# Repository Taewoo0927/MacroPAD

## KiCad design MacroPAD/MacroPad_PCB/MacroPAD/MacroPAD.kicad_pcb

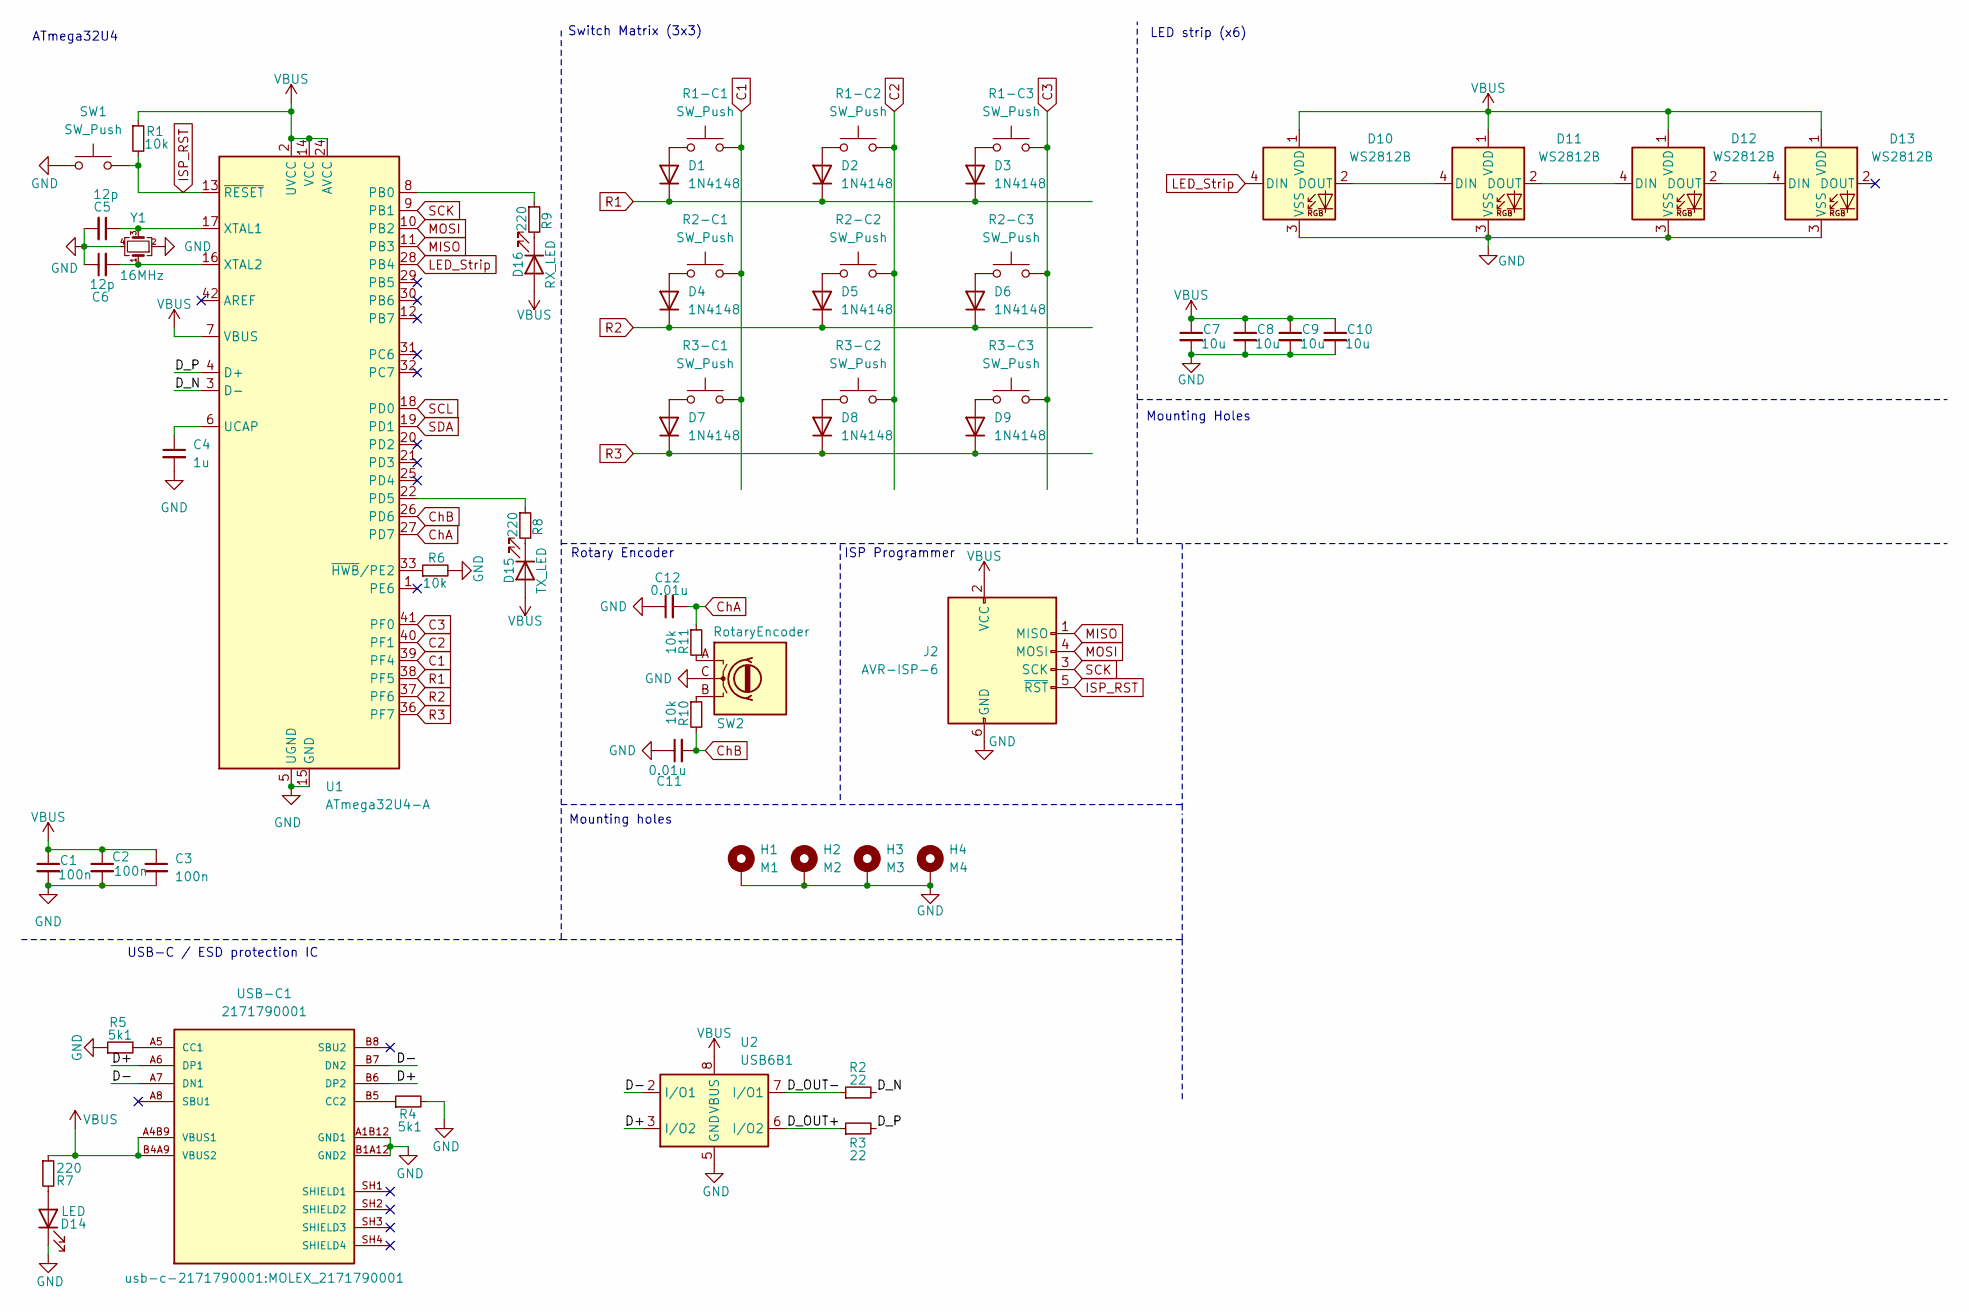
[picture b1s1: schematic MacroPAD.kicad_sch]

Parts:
C1, C2, C3: 100n; C_0603_1608Metric; MPN C0603C104K5RACTU
C4: 1u; C_0603_1608Metric; MPN CL10A105KB8NNNC
C5, C6: 12p; C_0603_1608Metric; MPN CL10C120JB8NNNC
C7, C8, C9, C10: 10u; C_0603_1608Metric; MPN C0603C106M8PACTU
C11, C12: 0.01u; C_0603_1608Metric; MPN C0603C103K5RACTU
D1, D2, D3, D4, D5, D6: 1N4148; D_SOD-123; MPN 1N4148W-13-F
D7, D8, D9: 1N4148; D_SOD-123
D10, D11, D12, D13: WS2812B; LED_WS2812B_PLCC4_5.0x5.0mm_P3.2mm; MPN COM-16347
D14: LED; LED_0805_2012Metric; MPN LG R971-KN-1-0-20-R18
D15: TX_LED; LED_1206_3216Metric; MPN LTST-C150YKT
D16: RX_LED; LED_1206_3216Metric; MPN LTST-C150KRKT
H1: M1; MountingHole_3.2mm_M3_Pad_Via
H2: M2; MountingHole_3.2mm_M3_Pad_Via
H3: M3; MountingHole_3.2mm_M3_Pad_Via
H4: M4; MountingHole_3.2mm_M3_Pad_Via
J2: AVR-ISP-6; IDC-Header_2x03_P2.54mm_Vertical; MPN 61200621621
R1: 10k; R_1206_3216Metric; MPN RC1206FR-0710KL
R1-C1, R1-C2, R1-C3, R2-C1, R2-C2, R2-C3, R3-C1, R3-C2, R3-C3: SW_Push; SW_Hotswap_Kailh_MX_1.00u; MPN PG151101S11
R2, R3: 22; R_0603_1608Metric; MPN RC0603FR-0722RL
R4, R5: 5k1; R_0603_1608Metric; MPN CR0603-FX-5101ELF
R6, R10, R11: 10k; R_0603_1608Metric; MPN RC0603FR-0710KL
R7: 220; R_0805_2012Metric; MPN CRGCQ0805F220R
R8, R9: 220; R_1206_3216Metric; MPN CRG1206F220R
SW1: SW_Push; SW_PUSH_6mm; MPN SKHHAKA010
SW2: RotaryEncoder; PEC12R-4XXXF-NXXXX_BRN; MPN PEC12R-4225F-N0024
U1: ATmega32U4-A; TQFP-44_10x10mm_P0.8mm; MPN ATmega32U4-A
U2: USB6B1; SOIC-8_3.9x4.9mm_P1.27mm; MPN USB6B1
USB-C1: 2171790001; MOLEX_2171790001; PARTREV A1
Y1: 16MHz; Crystal_SMD_0603-4Pin_6.0x3.5mm; MPN ECS-160-20-33-TR

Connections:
/D+: U2.3 (I/O2), USB-C1.A6 (DP1), USB-C1.B6 (DP2)
/D-: U2.2 (I/O1), USB-C1.A7 (DN1), USB-C1.B7 (DN2)
/D_N: R2.2, U1.3 (D-)
/D_OUT+: R3.1, U2.6 (I/O2)
/D_OUT-: R2.1, U2.7 (I/O1)
/D_P: R3.2, U1.4 (D+)
C1: R1-C1.2, R2-C1.2, R3-C1.2, U1.39 (PF4)
C2: R1-C2.2, R2-C2.2, R3-C2.2, U1.40 (PF1)
C3: R1-C3.2, R2-C3.2, R3-C3.2, U1.41 (PF0)
ChA: C12.2, R11.1, U1.27 (PD7)
ChB: C11.2, R10.2, U1.26 (PD6)
GND: C1.2, C2.2, C3.2, C4.2, C5.2, C6.1, C7.2, C8.2, C9.2, C10.2, C11.1, C12.1, D10.3 (VSS), D11.3 (VSS), D12.3 (VSS), D13.3 (VSS), D14.1 (K), H1.1, H2.1, H3.1, H4.1, J2.6 (GND), R4.2, R5.1, R6.2, SW1.1, SW2.C, U1.5 (UGND), U1.15 (GND), U1.23 (GND), U1.35 (GND), U1.43 (GND), U2.4 (GND), U2.5 (GND), USB-C1.A1B12 (GND1), USB-C1.B1A12 (GND2), Y1.2, Y1.4
ISP_RST: J2.5 (~RST), R1.2, SW1.2, U1.13 (~RESET)
LED_Strip: D10.4 (DIN), U1.28 (PB4)
MISO: J2.1 (MISO), U1.11 (PB3)
MOSI: J2.4 (MOSI), U1.10 (PB2)
unnamed: D1.2 (A), R1-C1.1
unnamed: D2.2 (A), R1-C2.1
unnamed: D3.2 (A), R1-C3.1
unnamed: D4.2 (A), R2-C1.1
unnamed: D5.2 (A), R2-C2.1
unnamed: D6.2 (A), R2-C3.1
unnamed: D7.2 (A), R3-C1.1
unnamed: D8.2 (A), R3-C2.1
unnamed: D9.2 (A), R3-C3.1
unnamed: D10.2 (DOUT), D11.4 (DIN)
unnamed: D11.2 (DOUT), D12.4 (DIN)
unnamed: D12.2 (DOUT), D13.4 (DIN)
unnamed: D14.2 (A), R7.2
unnamed: D15.1 (K), R8.2
unnamed: D16.1 (K), R9.2
unnamed: R10.1, SW2.B
unnamed: R11.2, SW2.A
unnamed: R9.1, U1.8 (PB0)
unnamed: R8.1, U1.22 (PD5)
unnamed: C4.1, U1.6 (UCAP)
unnamed: C5.1, U1.17 (XTAL1), Y1.3
unnamed: C6.2, U1.16 (XTAL2), Y1.1
unnamed: R6.1, U1.33 (~HWB/PE2)
unnamed: R5.2, USB-C1.A5 (CC1)
unnamed: R4.1, USB-C1.B5 (CC2)
R1: D1.1 (K), D2.1 (K), D3.1 (K), U1.38 (PF5)
R2: D4.1 (K), D5.1 (K), D6.1 (K), U1.37 (PF6)
R3: D7.1 (K), D8.1 (K), D9.1 (K), U1.36 (PF7)
SCK: J2.3 (SCK), U1.9 (PB1)
SCL: U1.18 (PD0)
SDA: U1.19 (PD1)
VBUS: C1.1, C2.1, C3.1, C7.1, C8.1, C9.1, C10.1, D10.1 (VDD), D11.1 (VDD), D12.1 (VDD), D13.1 (VDD), D15.2 (A), D16.2 (A), J2.2 (VCC), R1.1, R7.1, U1.2 (UVCC), U1.7 (VBUS), U1.14 (VCC), U1.24 (AVCC), U1.34 (VCC), U1.44 (AVCC), U2.1 (VBUS), U2.8 (VBUS), USB-C1.A4B9 (VBUS1), USB-C1.B4A9 (VBUS2)

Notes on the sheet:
ATmega32U4
USB-C / ESD protection IC
Mounting holes
LED strip (x6)
ISP Programmer
Rotary Encoder
Mounting Holes
Switch Matrix (3x3)

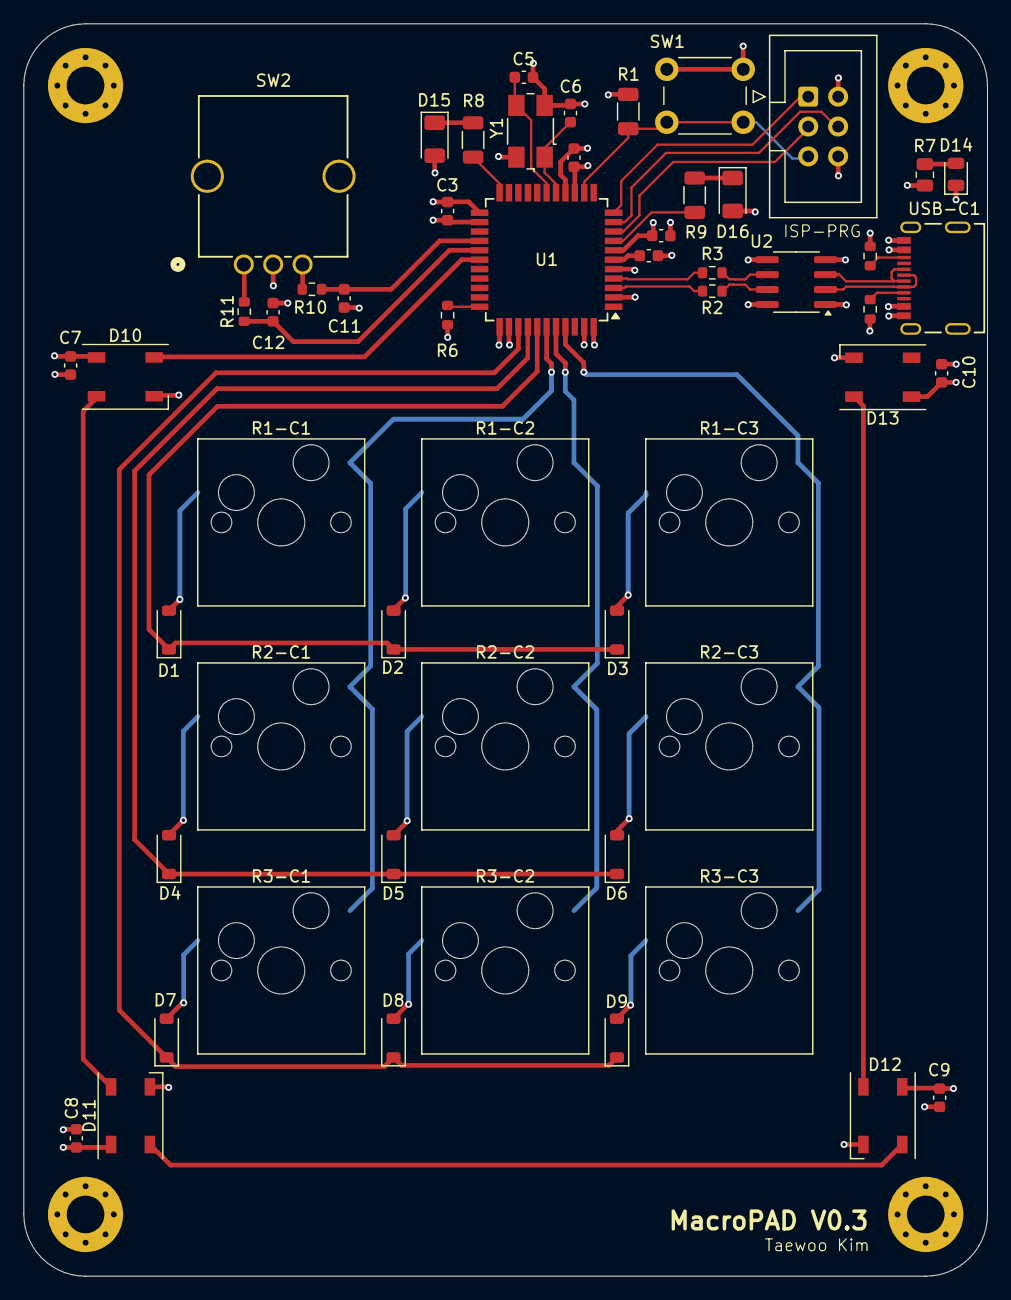
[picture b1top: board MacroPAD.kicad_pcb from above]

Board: 4 copper layers, 81.9 x 106.5 mm, 59 parts (0 on the bottom side), 46 nets.

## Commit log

2024-12-30 MacroPAD PCB
    Uploaded PCB
2025-01-04 <MacroPAD>
2025-01-04 Changing c-type input with differential pairs
2025-01-04 Fixed C-type
2025-01-04 Added ISR Debugg port
2025-01-05 Fixed macropad ISR programmer
2025-01-06 MacroPAD V0.3: Added additional filter for rotary encoder for debounce purpose
2025-01-06 Added MPN for the BOM
2025-01-11 Forgot to commit
